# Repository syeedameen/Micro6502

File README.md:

# A 6502 Microprocessor based Simple Computer (Currently under development)

## Features 
- TODO

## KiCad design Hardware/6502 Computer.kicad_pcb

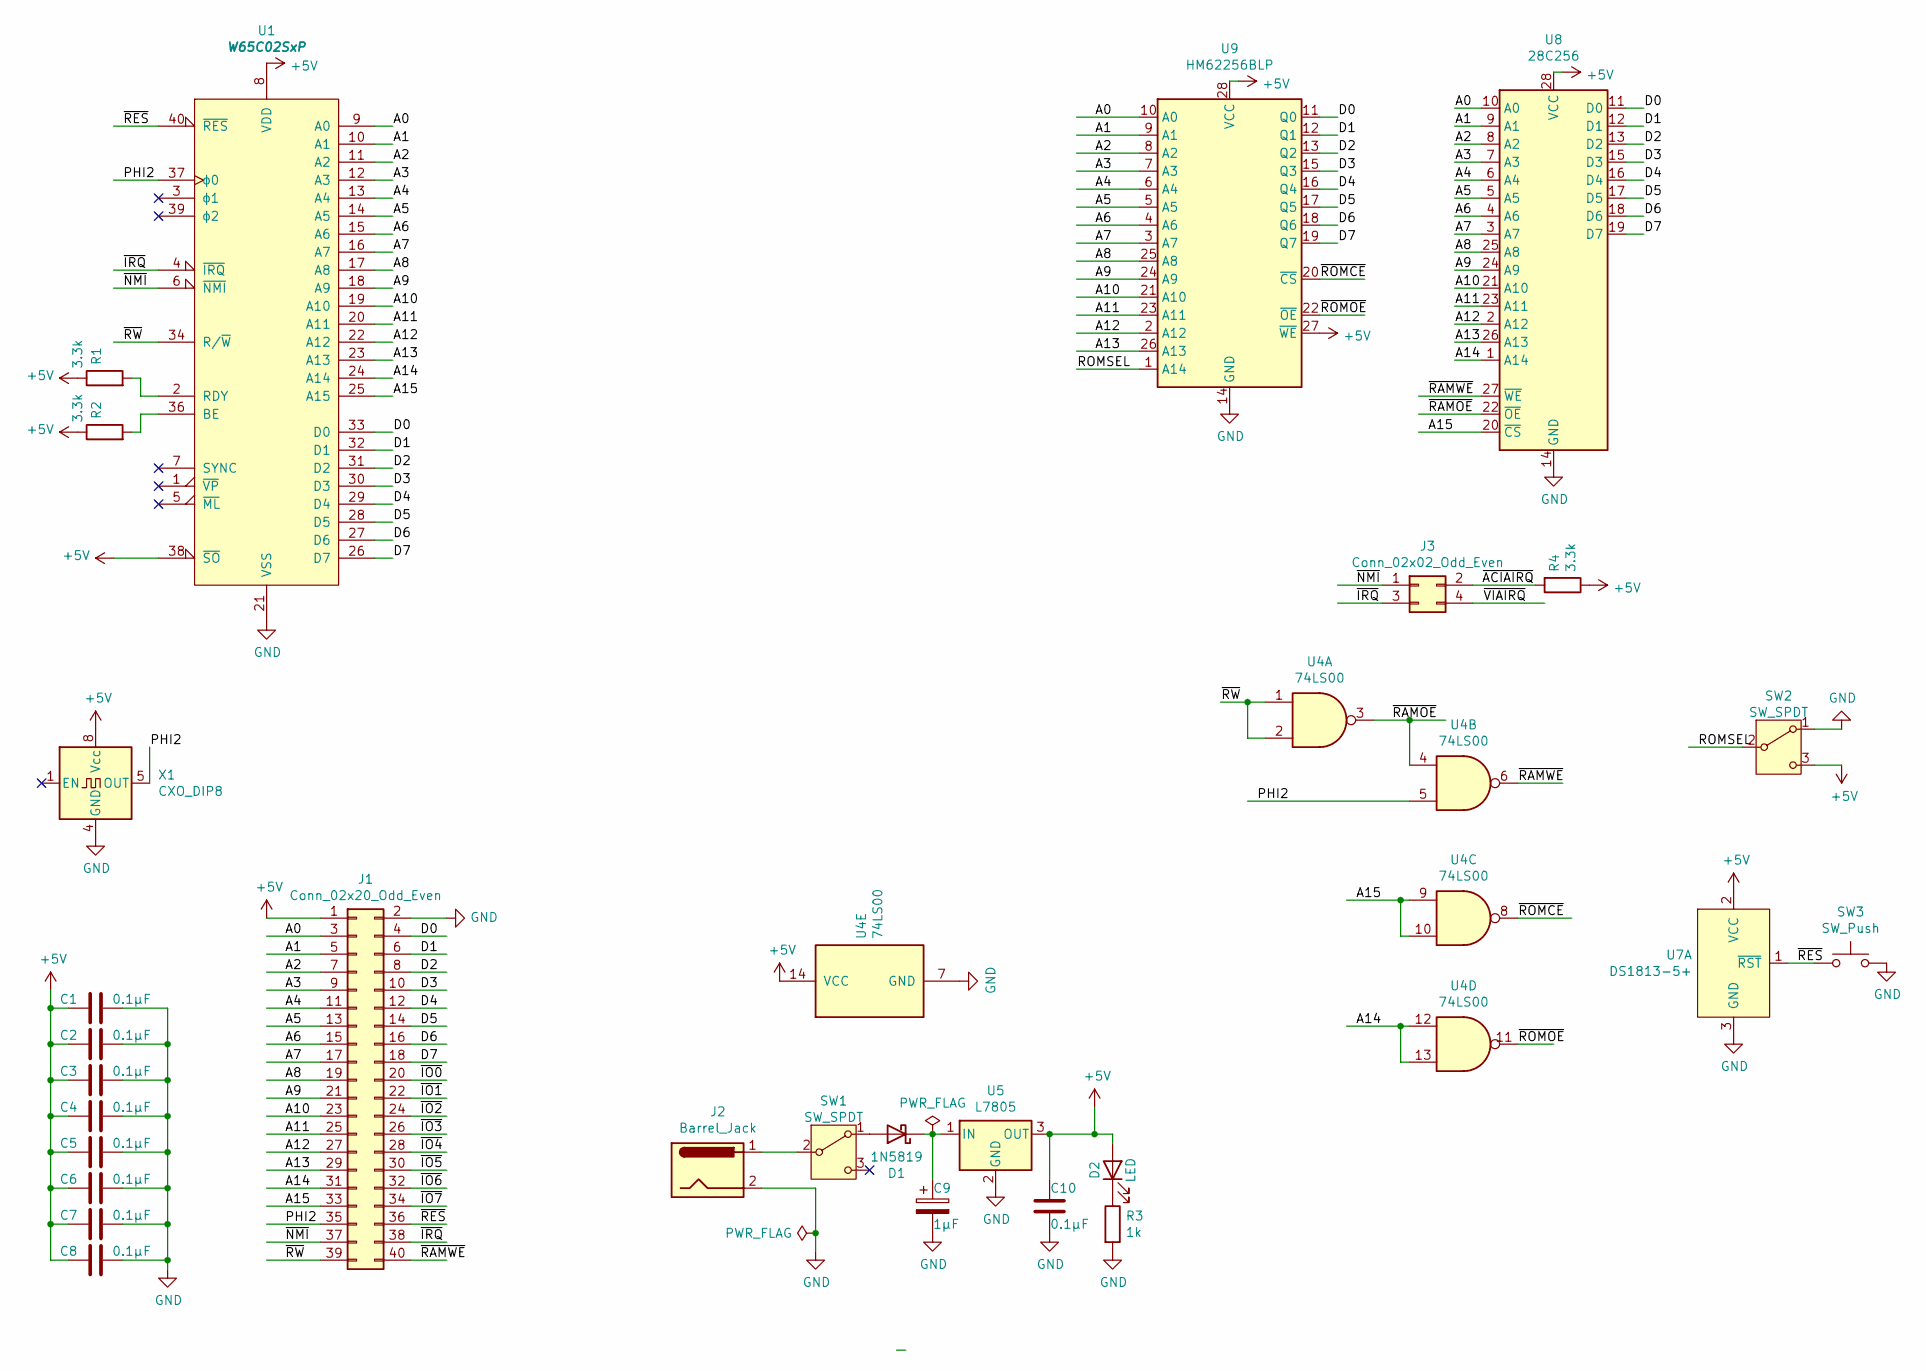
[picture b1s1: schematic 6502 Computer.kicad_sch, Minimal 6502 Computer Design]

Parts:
C1, C2, C3, C4, C5, C6, C7, C8, C10: 0.1µF; C_Disc_D5.0mm_W2.5mm_P2.50mm
C9: 1µF; C_Radial_D4.0mm_H7.0mm_P1.50mm
D1: 1N5819; D_DO-41_SOD81_P10.16mm_Horizontal
D2: LED; LED_D5.0mm
J1: Conn_02x20_Odd_Even; PinHeader_2x20_P2.54mm_Vertical
J2: Barrel_Jack; BarrelJack_Horizontal
J3: Conn_02x02_Odd_Even; PinHeader_2x02_P2.54mm_Vertical
R1, R2, R4: 3.3k; R_Axial_DIN0207_L6.3mm_D2.5mm_P10.16mm_Horizontal
R3: 1k; R_Axial_DIN0207_L6.3mm_D2.5mm_P10.16mm_Horizontal
SW1, SW2: SW_SPDT; SW_CuK_JS202011CQN_DPDT_Straight
SW3: SW_Push; SW_Tactile_Straight_KSL0Axx1LFTR
U1: W65C02SxP; DIP-40_W15.24mm_Socket
U4: 74LS00; DIP-14_W7.62mm_Socket
U5: L7805; TO-220-3_Horizontal_TabDown
U7: DS1813-5+; TO-92
U8: 28C256; DIP-28_W15.24mm_Socket
U9: HM62256BLP; DIP-28_W15.24mm_Socket
X1: CXO_DIP8; Oscillator_DIP-8

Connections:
+5V: C1.2, C2.2, C3.2, C4.2, C5.2, C6.2, C7.2, C8.2, C10.1, D2.2 (A), J1.1, R1.1, R2.1, R4.1, SW2.3 (C), U1.8 (VDD), U1.38 (~SO), U4.14 (VCC), U5.3 (OUT), U7.2 (VCC), U8.28 (VCC), U9.27 (~WE), U9.28 (VCC), X1.8 (Vcc)
/A0: J1.3, U1.9 (A0), U8.10 (A0), U9.10 (A0)
/A1: J1.5, U1.10 (A1), U8.9 (A1), U9.9 (A1)
/A2: J1.7, U1.11 (A2), U8.8 (A2), U9.8 (A2)
/A3: J1.9, U1.12 (A3), U8.7 (A3), U9.7 (A3)
/A4: J1.11, U1.13 (A4), U8.6 (A4), U9.6 (A4)
/A5: J1.13, U1.14 (A5), U8.5 (A5), U9.5 (A5)
/A6: J1.15, U1.15 (A6), U8.4 (A6), U9.4 (A6)
/A7: J1.17, U1.16 (A7), U8.3 (A7), U9.3 (A7)
/A8: J1.19, U1.17 (A8), U8.25 (A8), U9.25 (A8)
/A9: J1.21, U1.18 (A9), U8.24 (A9), U9.24 (A9)
/A10: J1.23, U1.19 (A10), U8.21 (A10), U9.21 (A10)
/A11: J1.25, U1.20 (A11), U8.23 (A11), U9.23 (A11)
/A12: J1.27, U1.22 (A12), U8.2 (A12), U9.2 (A12)
/A13: J1.29, U1.23 (A13), U8.26 (A13), U9.26 (A13)
/A14: J1.31, U1.24 (A14), U4.12, U4.13, U8.1 (A14)
/A15: J1.33, U1.25 (A15), U4.9, U4.10, U8.20 (~CS)
/D0: J1.4, U1.33 (D0), U8.11 (D0), U9.11 (Q0)
/D1: J1.6, U1.32 (D1), U8.12 (D1), U9.12 (Q1)
/D2: J1.8, U1.31 (D2), U8.13 (D2), U9.13 (Q2)
/D3: J1.10, U1.30 (D3), U8.15 (D3), U9.15 (Q3)
/D4: J1.12, U1.29 (D4), U8.16 (D4), U9.16 (Q4)
/D5: J1.14, U1.28 (D5), U8.17 (D5), U9.17 (Q5)
/D6: J1.16, U1.27 (D6), U8.18 (D6), U9.18 (Q6)
/D7: J1.18, U1.26 (D7), U8.19 (D7), U9.19 (Q7)
/PHI2: J1.35, U1.37 (ϕ0), U4.5, X1.5 (OUT)
/ROMSEL: SW2.2 (B), U9.1 (A14)
/~ACIAIRQ: J3.2, R4.2
/~IO0: J1.20
/~IO1: J1.22
/~IO2: J1.24
/~IO3: J1.26
/~IO4: J1.28
/~IO5: J1.30
/~IO6: J1.32
/~IO7: J1.34
/~IRQ: J1.38, J3.3, U1.4 (~IRQ)
/~NMI: J1.37, J3.1, U1.6 (~NMI)
/~RAMOE: U4.3, U4.4, U8.22 (~OE)
/~RAMWE: J1.40, U4.6, U8.27 (~WE)
/~RES: J1.36, SW3.1, U1.40 (~RES), U7.1 (~RST)
/~ROMCE: U4.8, U9.20 (~CS)
/~ROMOE: U4.11, U9.22 (~OE)
/~RW: J1.39, U1.34 (R/~W), U4.1, U4.2
/~VIAIRQ: J3.4
GND: C1.1, C2.1, C3.1, C4.1, C5.1, C6.1, C7.1, C8.1, C9.2, C10.2, J1.2, J2.2, R3.2, SW2.1 (A), SW3.2, U1.21 (VSS), U4.7 (GND), U5.2 (GND), U7.3 (GND), U8.14 (GND), U9.14 (GND), X1.4 (GND)
unnamed: D1.2 (A), SW1.1 (A)
unnamed: C9.1, D1.1 (K), U5.1 (IN)
unnamed: D2.1 (K), R3.1
unnamed: J2.1, SW1.2 (B)
unnamed: R2.2, U1.36 (BE)
unnamed: R1.2, U1.2 (RDY)

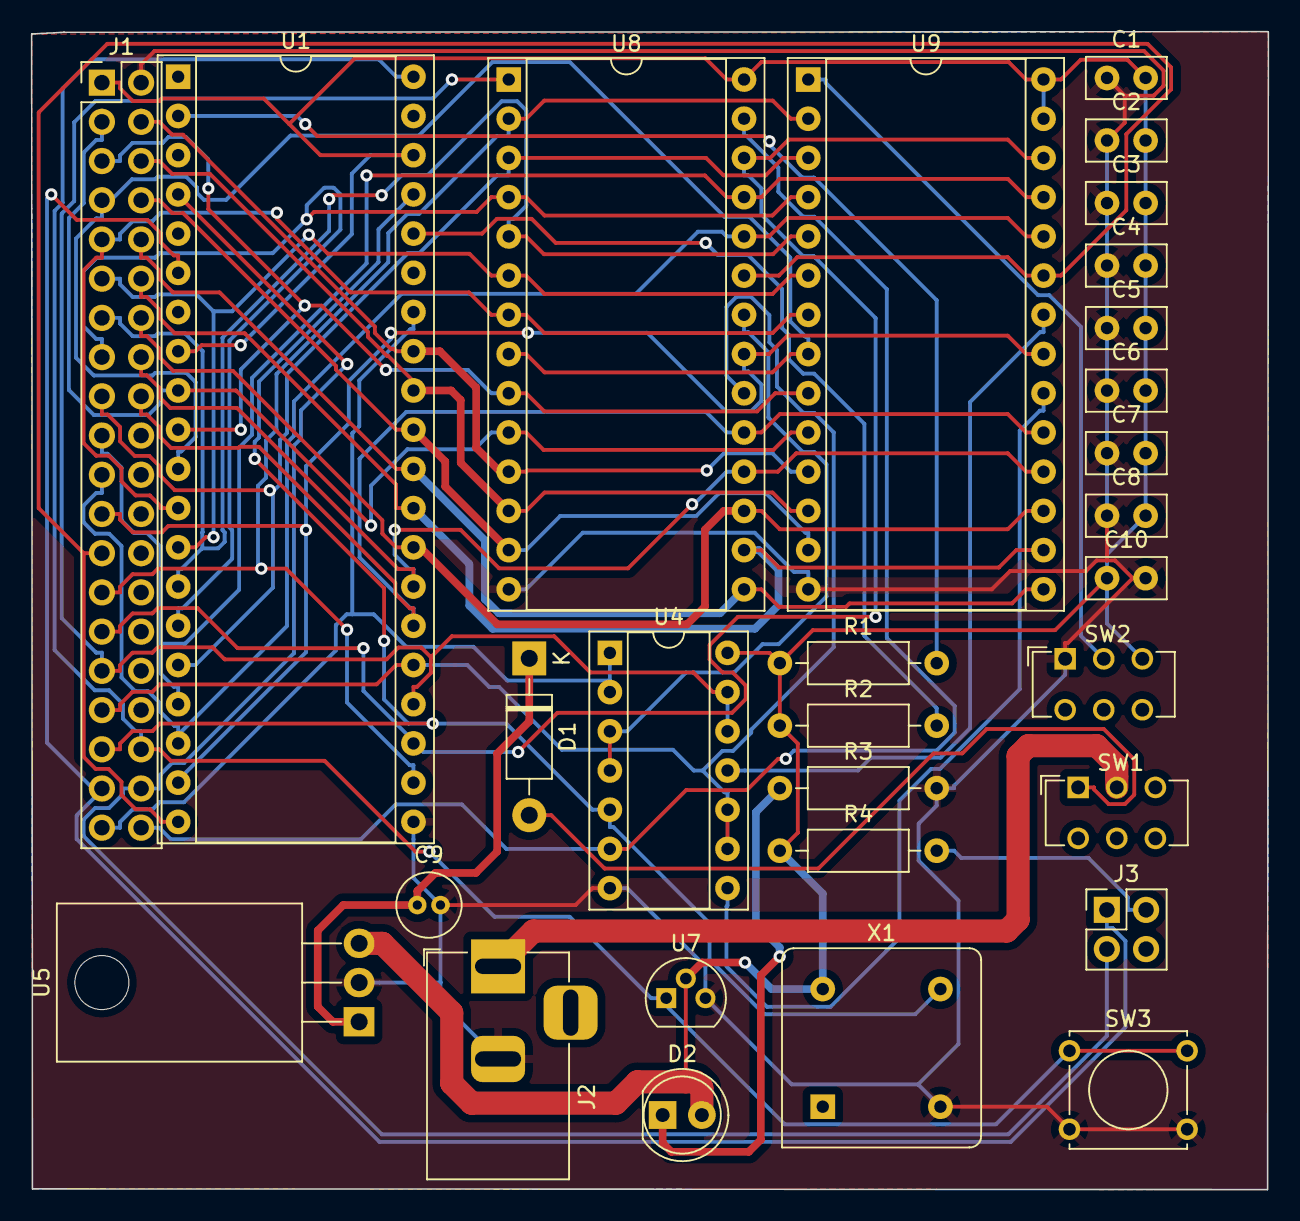
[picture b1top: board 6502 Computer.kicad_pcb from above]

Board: 2 copper layers, 80.1 x 75.0 mm, 29 parts (0 on the bottom side), 43 nets.
